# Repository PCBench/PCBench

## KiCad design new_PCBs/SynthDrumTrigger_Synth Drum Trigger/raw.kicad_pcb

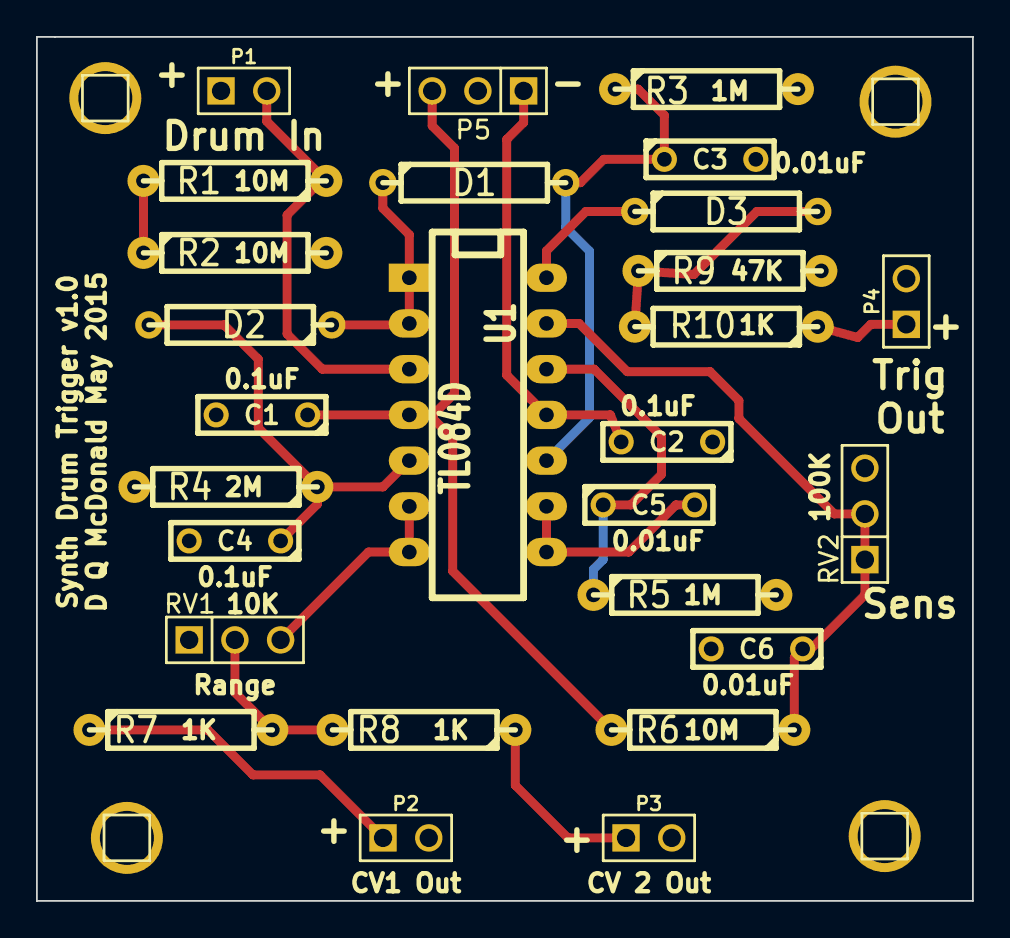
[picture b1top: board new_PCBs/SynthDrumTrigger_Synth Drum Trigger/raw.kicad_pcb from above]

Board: 2 copper layers, 52.0 x 48.0 mm, 27 parts (0 on the bottom side), 18 nets.

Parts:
C1, C2, C4: 0.1uF; C2
C3, C6: 0.01uF; C2
C5: 0.01; C2
D1, D2, D3: DIODE; R4
P1, P2, P3, P4: CONN_2; PIN_ARRAY_2X1
P5: Power_In; PIN_ARRAY_3X1
R1, R2, R6: 10M; R4-LARGE_PADS
R3, R5: 1M; R4-LARGE_PADS
R4: 2M; R4-LARGE_PADS
R7, R8, R10: 1K; R4-LARGE_PADS
R9: 47K; R4-LARGE_PADS
RV1: 10K; PIN_ARRAY_3X1
RV2: 100K; PIN_ARRAY_3X1
U1: TL084D; DIP-14__300_ELL

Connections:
+12V: C1.1, P5.3, R6.2, U1.4
-12V: C2.2, P5.1, U1.11
GND: C1.2, C2.1, C3.2, C4.2, C6.2, P1.1, P2.2, P3.2, P4.2, P5.2, R2.2, R3.2, R4.2, R5.2, R9.2, RV1.1, RV2.3
unnamed: C3.1, D1.2, R3.1, U1.10
unnamed: C4.1, D2.2, R4.1, U1.5
unnamed: C5.1, R5.1, U1.12
unnamed: C5.2, U1.8, U1.9
unnamed: C6.1, R6.1, RV2.1, RV2.2, U1.13
unnamed: D1.1, D2.1, U1.1, U1.2
unnamed: D3.1, U1.14
unnamed: D3.2, R9.1, R10.2
unnamed: P1.2, R1.1, U1.3
unnamed: P2.1, R7.1
unnamed: P3.1, R8.1
unnamed: P4.1, R10.1
unnamed: R1.2, R2.1
unnamed: R7.2, R8.2, RV1.2
unnamed: RV1.3, U1.6, U1.7

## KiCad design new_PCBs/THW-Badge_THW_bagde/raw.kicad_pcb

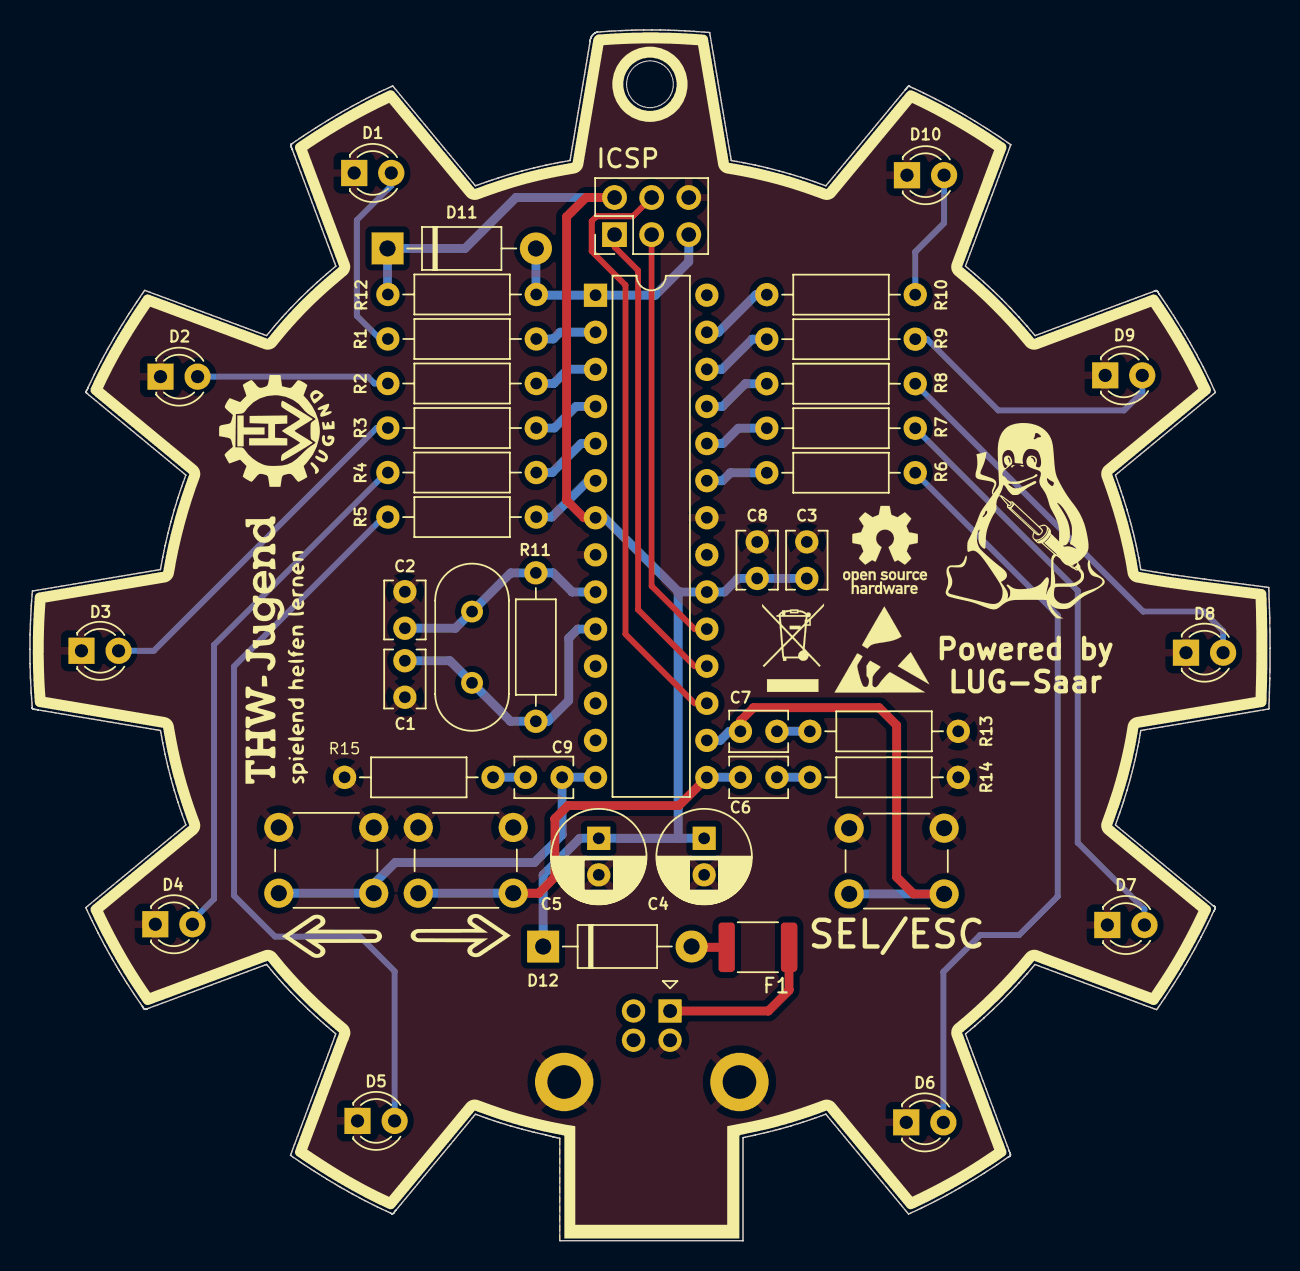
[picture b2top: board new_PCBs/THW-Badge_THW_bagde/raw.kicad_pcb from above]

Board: 2 copper layers, 84.9 x 82.9 mm, 44 parts (0 on the bottom side), 36 nets.

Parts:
C1, C2: C; C_Disc_D3.8mm_W2.6mm_P2.50mm
C3, C6, C7, C8, C9: 100n; C_Disc_D3.8mm_W2.6mm_P2.50mm
C4, C5: 100u; CP_Radial_D6.3mm_P2.50mm
D1, D2, D3, D4, D5, D6, D7, D8, D9, D10: LED; LED_D3.0mm_Clear
D11, D12: D; D_DO-41_SOD81_P10.16mm_Horizontal
F1: MF-MSMF050-2; Fuse_1812_4532Metric
J1: USB_B; USB_B_Lumberg_2411_02_Horizontal
J2: ICSP; PinHeader_2x03_P2.54mm_Vertical
R1, R2, R3, R4, R5, R6, R7, R8, R9, R10: R; R_Axial_DIN0207_L6.3mm_D2.5mm_P10.16mm_Horizontal
R11: 1M; R_Axial_DIN0207_L6.3mm_D2.5mm_P10.16mm_Horizontal
R12: 10K; R_Axial_DIN0207_L6.3mm_D2.5mm_P10.16mm_Horizontal
R13, R14, R15: 100; R_Axial_DIN0207_L6.3mm_D2.5mm_P10.16mm_Horizontal
SW1, SW2, SW3: SW_Push; SW_PUSH_6mm
U1: ATmega328-P; DIP-28_W7.62mm
Y1: Crystal; Crystal_HC49-4H_Vertical

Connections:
+5V: C3.1, C4.1, C5.1, C8.1, D11.1 (K), D12.1 (K), J2.2, R12.2, U1.7 (VCC), U1.20 (AVCC)
/MISO: J2.1, U1.18 (PB4)
/MOSI: J2.4, U1.17 (PB3)
/PB0: C9.1, SW1.2, U1.14 (PB0)
/PB1: C6.1, SW2.2, U1.15 (PB1)
/PB2: C7.1, SW3.2, U1.16 (PB2)
/PC0: R6.1, U1.23 (PC0)
/PC1: R7.1, U1.24 (PC1)
/PC2: R8.1, U1.25 (PC2)
/PC3: R9.1, U1.26 (PC3)
/PC4: R10.1, U1.27 (PC4)
/PD0: R1.1, U1.2 (PD0)
/PD1: R2.1, U1.3 (PD1)
/PD2: R3.1, U1.4 (PD2)
/PD3: R4.1, U1.5 (PD3)
/PD4: R5.1, U1.6 (PD4)
/RES: D11.2 (A), J2.5, R12.1, U1.1 (~RESET/PC6)
/SCK: J2.3, U1.19 (PB5)
GND: C1.2, C2.2, C3.2, C4.2, C5.2, C8.2, D1.1 (K), D2.1 (K), D3.1 (K), D4.1 (K), D5.1 (K), D6.1 (K), D7.1 (K), D8.1 (K), D9.1 (K), D10.1 (K), J1.4 (GND), J1.5 (Shield), J2.6, R13.1, R14.1, R15.1, SW1.1, SW2.1, SW3.1, U1.8 (GND), U1.22 (GND)
unnamed: C1.1, R11.1, U1.10 (XTAL2/PB7), Y1.1
unnamed: C2.1, R11.2, U1.9 (XTAL1/PB6), Y1.2
unnamed: C7.2, R13.2
unnamed: C9.2, R15.2
unnamed: D1.2 (A), R1.2
unnamed: D2.2 (A), R2.2
unnamed: D3.2 (A), R3.2
unnamed: D4.2 (A), R4.2
unnamed: D5.2 (A), R5.2
unnamed: D6.2 (A), R6.2
unnamed: D7.2 (A), R7.2
unnamed: D8.2 (A), R8.2
unnamed: D9.2 (A), R9.2
unnamed: D10.2 (A), R10.2
unnamed: D12.2 (A), F1.2
unnamed: F1.1, J1.1 (VBUS)
unnamed: C6.2, R14.2

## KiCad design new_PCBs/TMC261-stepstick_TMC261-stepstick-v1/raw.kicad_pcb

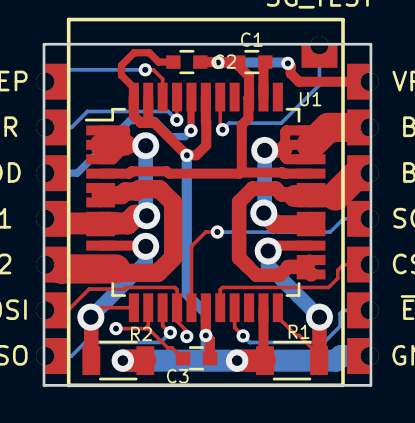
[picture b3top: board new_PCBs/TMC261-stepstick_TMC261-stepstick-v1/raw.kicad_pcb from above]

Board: 2 copper layers, 18.2 x 18.9 mm, 21 parts (0 on the bottom side), 19 nets.

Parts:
C1, C2: 100nF; C_0603
C3: 470nF; C_0603
P1: VDD; smd-edge
P2: MISO; smd-edge
P3: MOSI; smd-edge
P4: SCK; smd-edge
P5: ~EN; smd-edge
P6: CSN; smd-edge
P7: STEP; smd-edge
P8: DIR; smd-edge
P9: SG_TEST; smd-edge
P10: VPP; smd-edge
P11: GND; smd-edge
P12: B1; smd-edge
P13: B2; smd-edge
P14: A2; smd-edge
P15: A1; smd-edge
R1, R2: 150mR; C_1206
U1: TMC261; LQFP-44_10x10mm_Pitch0.8mm

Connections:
A1: P15.1, U1.1, U1.2, U1.3, U1.7, U1.8
A2: P14.1, U1.5, U1.6, U1.10, U1.11
B1: P12.1, U1.26, U1.27, U1.31, U1.32, U1.33
B2: P13.1, U1.23, U1.24, U1.28, U1.29
CSN: P6.1, U1.18
DIR: P8.1, U1.41
GND: C2.2, C3.2, P11.1, R1.2, R2.2, U1.17, U1.21, U1.39, U1.43, U1.44
MISO: P2.1, U1.14
MOSI: P3.1, U1.15
unnamed: C1.2, U1.35
unnamed: C3.1, U1.13
unnamed: R1.1, U1.22, U1.25
unnamed: R2.1, U1.9, U1.12
SCK: P4.1, U1.16
SG_TEST: P9.1, U1.38
STEP: P7.1, U1.42
VDD: P1.1, U1.40
VPP: C1.1, C2.1, P10.1, U1.4, U1.30, U1.36
~EN: P5.1, U1.19

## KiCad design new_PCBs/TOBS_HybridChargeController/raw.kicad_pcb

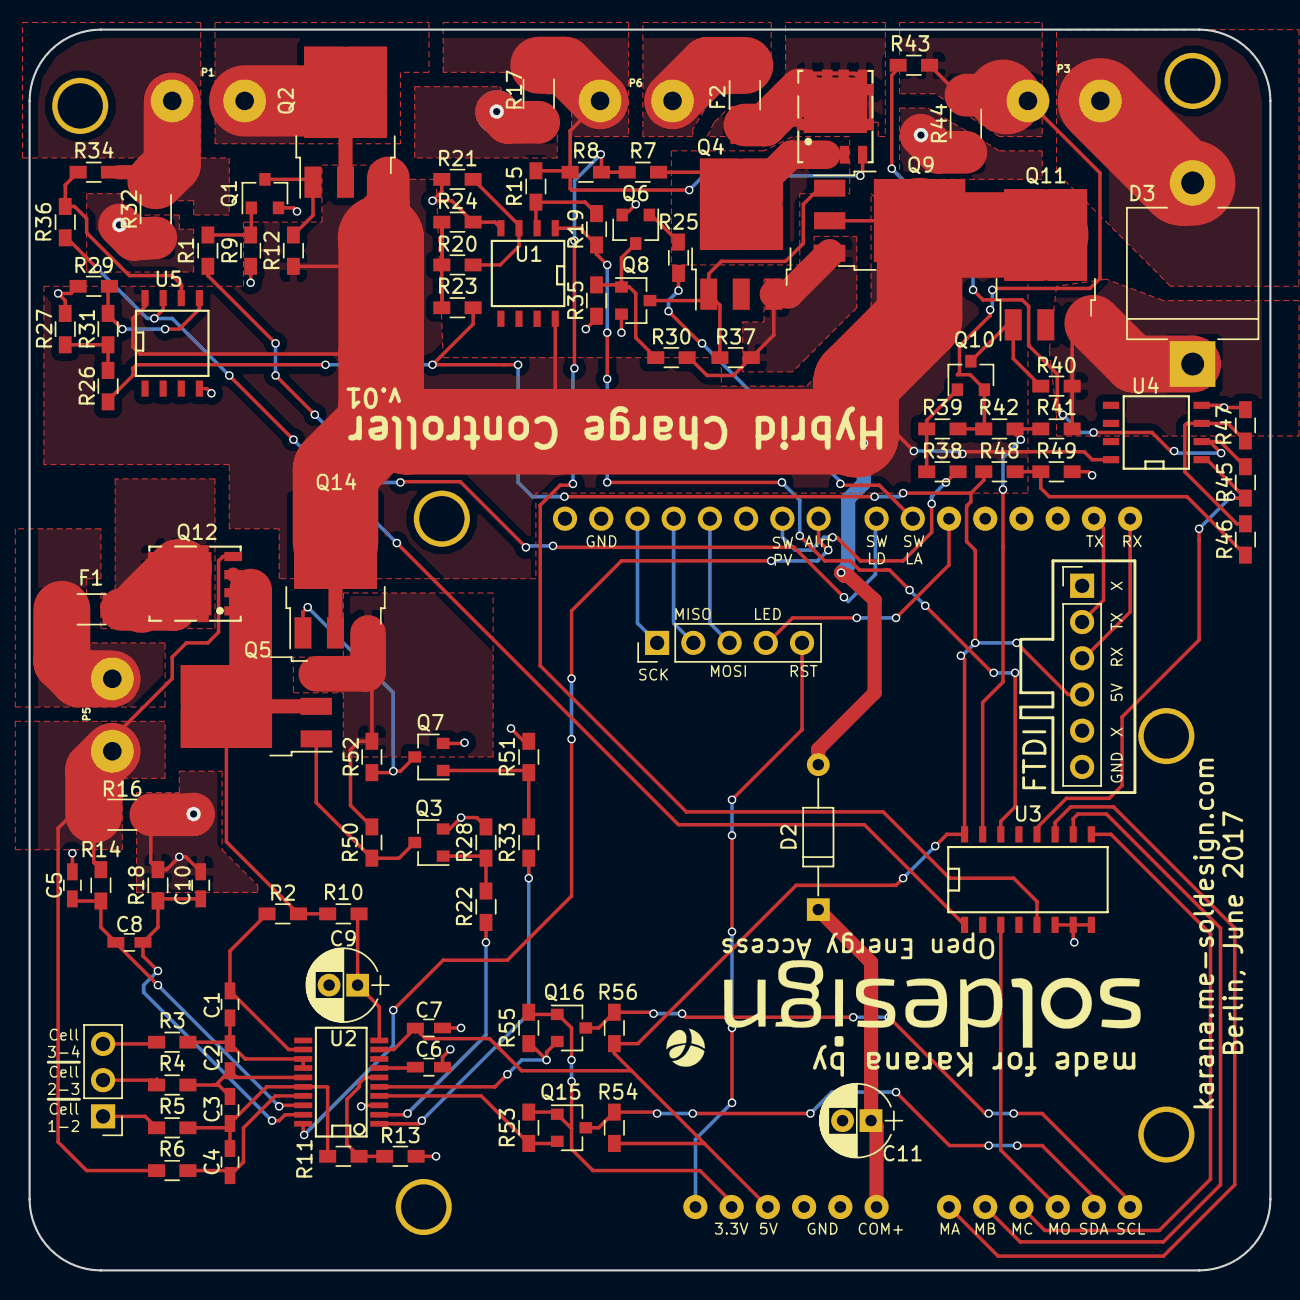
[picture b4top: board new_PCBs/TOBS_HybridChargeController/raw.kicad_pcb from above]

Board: 2 copper layers, 87.0 x 87.0 mm, 100 parts (0 on the bottom side), 79 nets.

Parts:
AU1: Uno Layout; ARDUINO_SHIELD_bigger_holes_no_outline
C1, C2, C3, C4, C6, C7: 1µ; C_0603_HandSoldering
C5, C8, C10: 0.1µ; C_0603_HandSoldering
C9, C11: 10µ; CP_Radial_D5.0mm_P2.00mm
D2: 1N4148-T; D_DO-35_SOD27_P10.16mm_Horizontal
D3: VSB2045Y-M3/54; D_P600_R-6_P12.70mm_Horizontal
F1, F2: 15A; Fuse_SMD1206_HandSoldering
P1: Load; TerminalBlock_Screw_2pol
P2: LI_balancer; Pin_Header_Straight_1x03_Pitch2.54mm
P3: PV; TerminalBlock_Screw_2pol
P4: Extra; Pin_Header_Straight_1x05_Pitch2.54mm
P5: LI; TerminalBlock_Screw_2pol
P6: LA; TerminalBlock_Screw_2pol
P7: FTDI; Pin_Header_Straight_1x06_Pitch2.54mm
Q1, Q3, Q6, Q7, Q8, Q10: MMBT3904; SOT-23
Q2, Q4, Q5, Q9, Q11, Q14: IPD90P04P4L-04; TO-252-3_TabPin2
Q12, Q13: STL60P4LLF6; powerFLAT_5x6_5..8com
Q15, Q16: BSS138; SOT-23
R1, R11, R13, R22, R23, R24, R25, R26, R27, R33, R38, R48, R49, R53, R54, R55, R56: 10k; R_0603_HandSoldering
R2, R3, R4, R5, R6, R10, R14, R18: 100; R_0603_HandSoldering
R7, R9, R28, R35, R39, R41, R51: 100k; R_0603_HandSoldering
R8, R42: 33k; R_0603_HandSoldering
R12, R30, R37, R50, R52: 47k; R_0603_HandSoldering
R15, R21, R29, R34, R43, R47: 4.7k; R_0603_HandSoldering
R16, R17, R32, R44: R005; R_1206_HandSoldering
R19, R20, R31, R36, R45, R46: 220k; R_0603_HandSoldering
R40: 2.2k; R_0603_HandSoldering
U1, U4, U5: LM358D; SOIC-8-N
U2: bq76920; SSOP-20
U3: cd4051; SO-16-N

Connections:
/3.3V: AU1.3V3, Q15.1, Q16.1, R53.1, R55.1
/5V: AU1.5V, C7.1, P7.4, R23.1, R26.1, R48.1, R54.1, R56.1, U2.9, U3.16
/Alert: AU1.8, U2.20
/CELL12: P2.1, R5.2
/CELL23: P2.2, R4.2
/CELL34: P2.3, R3.2
/CHG: R22.2, U2.2
/COM+: D2.2, Q2.3, Q9.2, Q11.2, Q14.2, R12.2, U1.8, U4.8, U5.8
/DSG: R33.2, U2.1
/GND: AU1.GND1, AU1.GND2, AU1.GND3, C5.2, C6.2, C7.2, C9.2, C10.2, C11.2, P7.6, Q1.2, Q3.2, Q6.2, Q7.2, Q8.2, R9.1, R13.2, R16.1, R17.1, R18.1, R21.1, R24.2, R27.2, R28.1, R29.1, R32.1, R35.1, R44.1, R47.1, R49.2, R51.1, U1.4, U2.3, U3.6, U3.7, U3.8, U4.4, U5.4
/LA+: Q4.2, Q13.1, Q13.2, Q13.3, R7.1
/LA-: P6.1, Q13.4, R8.2, R15.1, R17.2
/LED_BTN: AU1.5, P4.4
/LI+: Q5.2, Q12.1, Q12.2, Q12.3, R2.2, R10.2
/LI-: P5.1, Q12.4, R6.2, R14.1, R16.2
/LOAD+: P1.2, Q2.2
/LOAD-: P1.1, R32.2, R34.1
/MISO: AU1.12, P4.2
/MOSI: AU1.11, P4.3
/MplexA: AU1.A0, U3.11
/MplexB: AU1.A1, U3.10
/MplexC: AU1.A2, U3.9
/MplexOut: AU1.A3, U3.3
/PV+: D3.1, Q11.3, R40.2, R41.1
/PV-: P3.1, Q10.2, R39.1, R42.2, R43.1, R44.2
/RST: AU1.RST, P4.5
/RX: AU1.0, P7.3
/SCK: AU1.13, P4.1
/SCL3: Q16.2, R55.2, U2.5
/SCL5: AU1.A5, Q16.3, R56.2
/SDA3: Q15.2, R53.2, U2.4
/SDA5: AU1.A4, Q15.3, R54.2
/SRN: C8.1, C10.1, R18.2, U2.19
/SRP: C5.1, C8.2, R14.2, U2.18
/SW_LA: AU1.6, R25.2
/SW_LD: AU1.7, R1.2
/SW_PV: AU1.9, R38.2
/S_LA_I: R19.1, U1.1, U3.14
/S_LA_V: R7.2, R8.1, U3.5
/S_LD_I: R36.2, U3.1, U5.7
/S_PV_I: R45.1, U3.12, U4.1
/S_PV_V: R41.2, R42.1, U3.15
/TX: AU1.1, P7.2
/VC0: C4.2, R6.1, U2.17
/VC1: C3.2, C4.1, R5.1, R11.2, U2.16
/VC2: C2.2, C3.1, R4.1, U2.15
/VC3: C1.2, C2.1, R3.1, U2.13, U2.14
/VC5: C1.1, R2.1, U2.12
unnamed: AU1.V_IN, C11.1, D2.1
unnamed: C6.1, U2.7
unnamed: C9.1, R10.1, U2.10
unnamed: D3.2, P3.2
unnamed: F1.1, P5.2
unnamed: F1.2, Q12.5, Q12.6, Q12.7, Q12.8
unnamed: F2.1, P6.2
unnamed: F2.2, Q13.5, Q13.6, Q13.7, Q13.8
unnamed: Q1.1, R1.1, R9.2
unnamed: Q1.3, Q2.1, R12.1
unnamed: Q3.1, R22.1, R28.2
unnamed: Q3.3, Q5.1, R50.2
unnamed: Q4.1, Q8.3, Q9.1, R37.1
unnamed: Q4.3, Q9.3, R30.2, R37.2
unnamed: Q6.1, R25.1
unnamed: Q6.3, Q8.1, R30.1, R35.2
unnamed: Q7.1, R33.1, R51.2
unnamed: Q10.1, R38.1, R39.2
unnamed: Q10.3, Q11.1, R40.1
unnamed: Q7.3, Q14.1, R52.1
unnamed: Q5.3, Q14.3, R50.1, R52.2
unnamed: R11.1, R13.1, U2.6
unnamed: R15.2, R19.2, U1.2
unnamed: R20.1, R23.2, R24.1
unnamed: R20.2, R21.2, U1.3
unnamed: R26.2, R27.1, R31.1
unnamed: R29.2, R31.2, U5.5
unnamed: R34.2, R36.1, U5.6
unnamed: R43.2, R45.2, U4.2
unnamed: R46.1, R48.2, R49.1
unnamed: R46.2, R47.2, U4.3

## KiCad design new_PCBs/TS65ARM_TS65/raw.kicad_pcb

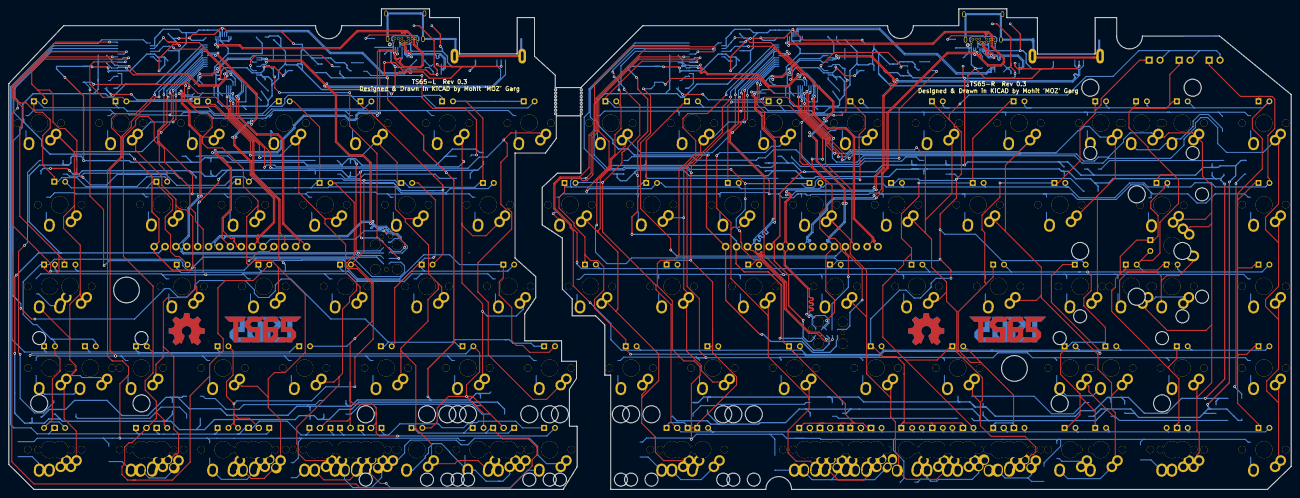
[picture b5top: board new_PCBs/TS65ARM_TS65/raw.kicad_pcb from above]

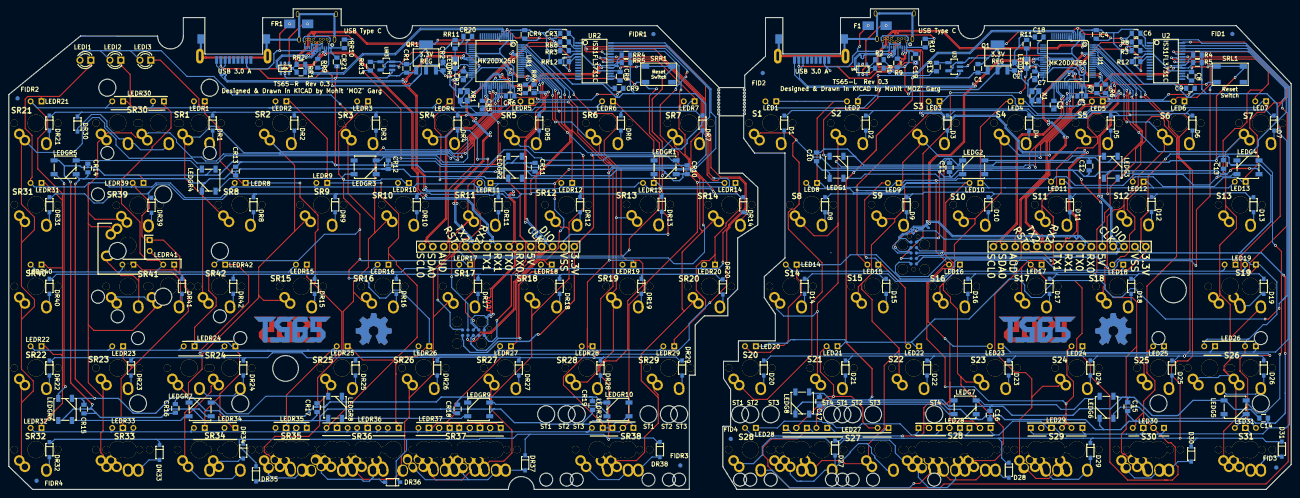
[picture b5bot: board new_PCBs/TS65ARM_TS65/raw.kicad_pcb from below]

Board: 2 copper layers, 299.2 x 112.1 mm, 438 parts (198 on the bottom side), 208 nets.

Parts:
BREAKHOLES1, BREAKHOLES2: MISC; BreakHoles
C1, C2, C3: 1uF; SMD_0805
C4, C5, C6, C7, C8, C18: 0.1uF; SMD_0805
C9: 0.22uF; SMD_0805
C10, C11, C12, C13, C14, C15, C16, C17: 0.1 uF; SMD_0805
C19: 10uF; SMD_0805
CR1, CR2, CR3: 1uF; SMD_0805
CR4, CR5, CR6, CR7, CR8, CR20: 0.1uF; SMD_0805
CR9: 0.22uF; SMD_0805
CR10, CR11, CR12, CR13, CR14, CR15, CR16, CR17, CR18, CR19: 0.1 uF; SMD_0805
CR21: 10uF; SMD_0805
D1, D2, D3, D4, D5, D6, D7, D8, D9, D10, D11, D12, D13, D14, D15, D16, D17, D18, D19, D20, D21, D22, D23, D24, D25, D26, D27, D28, D29, D30, D31: DIODE; SOD123-DIODE
DR1, DR2, DR3, DR4, DR5, DR6, DR7, DR8, DR9, DR10, DR11, DR12, DR13, DR14, DR15, DR16, DR17, DR18, DR19, DR20, DR21, DR22, DR23, DR24, DR25, DR26, DR27, DR28, DR29, DR30, DR31, DR32, DR33, DR34, DR35, DR36, DR37, DR38, DR39, DR40, DR41, DR42: DIODE; SOD123-DIODE
F1: PTC FUSE; Fuse_SMD1206_HandSoldering
FID1, FID2, FID3, FID4: MISC; FID
FIDR1, FIDR2, FIDR3, FIDR4: MISC; FID
FR1: PTC FUSE; Fuse_SMD1206_HandSoldering
HOLE1: MISC; FID
HOLER1: MISC; FID
LED1, LED2, LED3, LED4, LED5, LED6, LED7, LED8, LED9, LED10, LED11, LED12, LED13, LED14, LED15, LED16, LED17, LED18, LED19, LED19_2, LED20, LED21, LED22, LED23, LED24, LED25, LED26, LED26_2, LED27, LED27_2, LED27_3, LED27_4, LED28, LED28_2, LED28_3, LED28_4, LED28_5, LED28_6, LED28_7, LED29, LED29_2, LED29_3, LED29_4, LED30, LED30_2, LED30_3, LED31, LED31_2: LED; INSW_LEDS_REG
LEDD1: LED; LED_0805
LEDDR1: LED; LED_0805
LEDG1, LEDG2, LEDG3, LEDG4, LEDG5, LEDG6, LEDG7, LEDG8: WS2812B
LEDGR1, LEDGR2, LEDGR3, LEDGR4, LEDGR5, LEDGR6, LEDGR7, LEDGR8, LEDGR9, LEDGR10: WS2812B
LEDI1, LEDI2, LEDI3: LED; LED-3MM
LEDR1, LEDR2, LEDR3, LEDR4, LEDR5, LEDR6, LEDR7, LEDR8, LEDR9, LEDR10, LEDR11, LEDR12, LEDR13, LEDR14, LEDR15, LEDR16, LEDR17, LEDR18, LEDR19, LEDR20, LEDR21, LEDR22, LEDR23, LEDR24, LEDR24_2, LEDR25, LEDR26, LEDR27, LEDR28, LEDR29, LEDR30, LEDR30_2, LEDR31, LEDR32, LEDR33, LEDR33_2, LEDR34, LEDR34_2, LEDR35, LEDR35_2, LEDR35_3, LEDR36, LEDR36_2, LEDR36_3, LEDR36_4, LEDR36_5, LEDR37, LEDR37_2, LEDR37_3, LEDR37_4, LEDR37_5, LEDR37_6, LEDR37_7, LEDR38, LEDR38_2, LEDR38_3, LEDR39, LEDR40, LEDR41, LEDR41_2, LEDR41_3, LEDR42: LED; INSW_LEDS_REG
LOGO1, LOGO2: MISC; TS65-LOGO
LOGO3, LOGO4: MISC; OSHW
LOGOR1, LOGOR2: MISC; TS65-LOGO
LOGOR3, LOGOR4: MISC; OSHW
P1: USB_TYPE_C; USB_TYPE_C_HYBRID
P2: USB3_AFEMALE; USB3_AFEMALE_MOD
P3: CONN_15; HEADER_1x15
P4: FLASH_HDR; JLINK_NEEDLE
PR1: USB_TYPE_C; USB_TYPE_C_HYBRID
PR2: USB3_AFEMALE; USB3_AFEMALE_MOD
PR3: CONN_15; HEADER_1x15
PR4: FLASH_HDR; JLINK_NEEDLE
Q1: 3.3V REG IC; SOT-223
QR1: 3.3V REG IC; SOT-223
R1, R2: 33; SMD_0805
R3, R4, R5: 4.7k; SMD_0805
R6, R7: 100; SMD_0805
R8: 100k; SMD_0805
R9, R10: 5.1k; SMD_0805
R11: 1k; SMD_0805
R12: 20k; SMD_0805
R13: 330; SMD_0805
RR1, RR2: 33; SMD_0805
RR3, RR4, RR5: 4.7k; SMD_0805
RR6, RR7: 100; SMD_0805
RR8: 100k; SMD_0805
RR9, RR10: 5.1k; SMD_0805
RR11: 1k; SMD_0805
RR12: 20k; SMD_0805
RR13: 330; SMD_0805
S1, S2, S3, S4, S5, S6, S7, S8, S9, S10, S11, S12, S13, S14, S15, S16, S17, S18, S19, S19_2, S20, S21, S22, S23, S24, S25, S26, S26_2, S27, S27_2, S27_3, S27_4, S28, S28_2, S28_3, S28_4, S28_5, S28_6, S28_7, S29, S29_2, S29_3, S29_4, S30, S30_2, S30_3, S31, S31_2: SW; MXALPS2
SR1, SR2, SR3, SR4, SR5, SR6, SR7, SR8, SR9, SR10, SR11, SR12, SR13, SR14, SR15, SR16, SR17, SR18, SR19, SR20, SR21, SR22, SR23, SR24, SR24_2, SR25, SR26, SR27, SR28, SR29, SR30, SR30_2, SR31, SR32, SR33, SR33_2, SR34, SR34_2, SR35, SR35_2, SR35_3, SR36, SR36_2, SR36_3, SR36_4, SR36_5, SR37, SR37_2, SR37_3, SR37_4, SR37_5, SR37_6, SR37_7, SR38, SR38_2, SR38_3, SR39, SR40, SR41, SR41_2, SR41_3, SR42: SW; MXALPS2
SRL1: TAC_SWITCH; TACT_5.2x5.2
SRR1: TAC_SWITCH; TACT_5.2x5.2
STAB1, STAB2, STAB3, STAB4, STAB5: MISC; MX_200
STABR1, STABR2, STABR3, STABR4, STABR5, STABR6, STABR7: MISC; MX_200
U1: MK20DX256VLH7; LQFP64
U2: IS31FL3731; SSOP-28
U3: 74HCT1G125; SOT-753
U4: IP4234CZ6; SOT457
UR1: MK20DX256VLH7; LQFP64
UR2: IS31FL3731; SSOP-28
UR3: 74HCT1G125; SOT-753
UR4: IP4234CZ6; SOT457
X1: CRYSTAL; NX3225SA
XR1: CRYSTAL; NX3225SA

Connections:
+5V: C1.1, C10.2, C11.2, C12.2, C13.2, C14.1, C15.1, C16.1, C17.1, C19.1, CR1.1, CR10.2, CR11.2, CR12.2, CR13.2, CR14.2, CR15.1, CR16.1, CR17.1, CR18.1, CR19.1, CR21.1, F1.2, FR1.2, LEDG1.1, LEDG2.1, LEDG3.1, LEDG4.1, LEDG5.1, LEDG6.1, LEDG7.1, LEDG8.1, LEDGR1.1, LEDGR2.1, LEDGR3.1, LEDGR4.1, LEDGR5.1, LEDGR6.1, LEDGR7.1, LEDGR8.1, LEDGR9.1, LEDGR10.1, P3.5, P4.5, PR3.5, PR4.5, Q1.1, QR1.1, U3.1, U4.5, UR3.1, UR4.5
/ledmatrix/CA1: LED1.2, LED2.1, LED3.1, LED4.1, LED5.1, LED6.2, LED10.2, LED15.2, LED23.2, LED28.2, LED28_2.2, LED28_3.2, LED28_4.2, LED28_5.2, LED28_6.2, LED28_7.2, U2.21
/ledmatrix/CA2: LED1.1, LED2.2, LED7.2, LED8.1, LED9.1, LED11.2, LED16.2, LED24.2, LED29.2, LED29_2.2, LED29_3.2, LED29_4.2, U2.22
/ledmatrix/CA3: LED3.2, LED6.1, LED7.1, LED12.2, LED13.1, LED14.1, LED17.2, LED20.2, LED25.2, LED30.2, LED30_2.2, LED30_3.2, U2.23
/ledmatrix/CA4: LED4.2, LED8.2, LED10.1, LED11.1, LED12.1, LED13.2, LED18.2, LED19.1, LED19_2.1, LED21.2, LED26.2, LED26_2.2, LED27.2, LED27_2.2, LED27_3.2, LED27_4.2, LED31.2, LED31_2.2, U2.24
/ledmatrix/CA5: LED5.2, LED9.2, LED14.2, LED15.1, LED16.1, LED17.1, LED18.1, LED19.2, LED19_2.2, LED22.2, U2.25
/ledmatrix/CA6: LED20.1, LED21.1, LED22.1, U2.26
/ledmatrix/CA7: LED23.1, LED24.1, LED25.1, LED26.1, LED26_2.1, U2.27
/ledmatrix/CA8: LED27.1, LED27_2.1, LED27_3.1, LED27_4.1, U2.28
/ledmatrix/CA9: LED28.1, LED28_2.1, LED28_3.1, LED28_4.1, LED28_5.1, LED28_6.1, LED28_7.1, LED29.1, LED29_2.1, LED29_3.1, LED29_4.1, LED30.1, LED30_2.1, LED30_3.1, LED31.1, LED31_2.1, U2.1
/ledmatrixR/CA1: LEDR1.2, LEDR2.2, LEDR3.2, LEDR4.2, LEDR5.2, LEDR6.2, LEDR7.1, LEDR21.2, LEDR22.1, LEDR30.2, LEDR30_2.2, LEDR31.1, LEDR32.1, LEDR40.1, UR2.21
/ledmatrixR/CA2: LEDI1.1, LEDR8.2, LEDR9.2, LEDR10.2, LEDR11.2, LEDR12.2, LEDR13.2, LEDR21.1, LEDR23.1, LEDR31.2, LEDR33.1, LEDR33_2.1, LEDR39.2, LEDR41.1, LEDR41_2.1, LEDR41_3.1, UR2.22
/ledmatrixR/CA3: LEDI2.1, LEDR15.2, LEDR16.2, LEDR17.2, LEDR18.2, LEDR19.2, LEDR20.2, LEDR24.1, LEDR24_2.1, LEDR30.1, LEDR30_2.1, LEDR34.1, LEDR34_2.1, LEDR39.1, LEDR40.2, LEDR41.2, LEDR41_2.2, LEDR41_3.2, UR2.23
/ledmatrixR/CA4: LEDI3.1, LEDR1.1, LEDR8.1, LEDR15.1, LEDR22.2, LEDR23.2, LEDR24.2, LEDR24_2.2, LEDR25.2, LEDR26.2, LEDR27.2, LEDR28.2, LEDR29.2, LEDR35.1, LEDR35_2.1, LEDR35_3.1, UR2.24
/ledmatrixR/CA5: LEDR2.1, LEDR9.1, LEDR14.2, LEDR16.1, LEDR25.1, LEDR32.2, LEDR33.2, LEDR33_2.2, LEDR34.2, LEDR34_2.2, LEDR35.2, LEDR35_2.2, LEDR35_3.2, LEDR36.2, LEDR36_2.2, LEDR36_3.2, LEDR36_4.2, LEDR36_5.2, LEDR37.2, LEDR37_2.2, LEDR37_3.2, LEDR37_4.2, LEDR37_5.2, LEDR37_6.2, LEDR37_7.2, LEDR38.2, LEDR38_2.2, LEDR38_3.2, UR2.25
/ledmatrixR/CA6: LEDI1.2, LEDI2.2, LEDI3.2, LEDR3.1, LEDR7.2, LEDR10.1, LEDR17.1, LEDR26.1, LEDR36.1, LEDR36_2.1, LEDR36_3.1, LEDR36_4.1, LEDR36_5.1, LEDR42.2, UR2.26
/ledmatrixR/CA7: LEDR4.1, LEDR11.1, LEDR18.1, LEDR27.1, LEDR37.1, LEDR37_2.1, LEDR37_3.1, LEDR37_4.1, LEDR37_5.1, LEDR37_6.1, LEDR37_7.1, UR2.27
/ledmatrixR/CA8: LEDR5.1, LEDR12.1, LEDR19.1, LEDR28.1, LEDR38.1, LEDR38_2.1, LEDR38_3.1, UR2.28
/ledmatrixR/CA9: LEDR6.1, LEDR13.1, LEDR14.1, LEDR20.1, LEDR29.1, LEDR42.1, UR2.1
/mcu/AUD: C9.2, P3.13
/mcu/GND: P1.0, P2.10
/mcu/INTB: R3.2, U1.40, U2.4
/mcu/MCU_RESET: C5.1, P3.12, P4.10, SRL1.2, U1.34
/mcu/PTA5: LEDD1.1, P4.9, U1.27
/mcu/PTA13: U1.29, U3.2
/mcu/PTB18: S1.1, S20.1, U1.41
/mcu/PTB19: S2.1, S8.1, S14.1, S21.1, U1.42
/mcu/PTC0: S3.1, S9.1, S15.1, S22.1, S27.1, S27_2.1, S27_3.1, S27_4.1, U1.43
/mcu/PTC9: S4.1, S10.1, S16.1, S23.1, S28.1, S28_2.1, S28_3.1, S28_4.1, S28_5.1, S28_6.1, S28_7.1, U1.54
/mcu/PTC10: S5.1, S11.1, S17.1, S24.1, S29.1, S29_2.1, S29_3.1, S29_4.1, U1.55
/mcu/PTC11: S6.1, S12.1, S18.1, S25.1, S30.1, S30_2.1, S30_3.1, U1.56
/mcu/PTD0: S7.1, S13.1, S19.1, S19_2.1, S26.1, S26_2.1, S31.1, S31_2.1, U1.57
/mcu/PTD1: D1.2, D2.2, D3.2, D4.2, D5.2, D6.2, D7.2, U1.58
/mcu/PTD4: D8.2, D9.2, D10.2, D11.2, D12.2, D13.2, U1.61
/mcu/PTD5: D14.2, D15.2, D16.2, D17.2, D18.2, D19.2, U1.62
/mcu/PTD6: D20.2, D21.2, D22.2, D23.2, D24.2, D25.2, D26.2, U1.63
/mcu/PTD7: D27.2, D28.2, D29.2, D30.2, D31.2, U1.64
/mcu/SCL0: P3.15, R4.2, U1.35, U2.20
/mcu/SDA0: P3.14, R5.2, U1.36, U2.19
/mcu/SDB: R8.2, U1.39, U2.3
/mcu/SWD_CLK: P3.4, P4.4, R6.2
/mcu/SWD_DIO: P3.3, P4.2, R7.2
/mcu/UART0+: P2.5, P3.7, P4.6, U1.24
/mcu/UART0-: P2.6, P3.6, P4.8, U1.23
/mcu/UART1+: P1.A2, P1.B2, P3.9, U1.1
/mcu/UART1-: P1.A3, P1.B3, P3.8, U1.2
/mcu/UART2+: P3.11, P4.7, U1.60
/mcu/UART2-: P3.10, U1.59
/mcu/USB_D+: R2.2, U1.5
/mcu/USB_D-: R1.2, U1.6
/mcu/USB_D_IN+: P1.A6, P1.B6, U4.3
/mcu/USB_D_IN-: P1.A7, P1.B7, U4.4
/mcu/VBUS: F1.1, P1.A4, P1.A9, P1.B4, P1.B9, P2.1
/mcuR/AUD: CR9.2, PR3.13
/mcuR/GND: PR1.0, PR2.10
/mcuR/INTB: RR3.2, UR1.40, UR2.4
/mcuR/MCU_RESET: CR5.1, PR3.12, PR4.10, SRR1.2, UR1.34
/mcuR/PTA5: LEDDR1.1, PR4.9, UR1.27
/mcuR/PTA13: UR1.29, UR3.2
/mcuR/PTB2: SR21.1, SR22.1, SR31.1, SR32.1, SR40.1, UR1.37
/mcuR/PTB3: SR23.1, SR30.1, SR30_2.1, SR33.1, SR33_2.1, SR39.1, SR41.1, SR41_2.1, SR41_3.1, UR1.38
/mcuR/PTB18: SR1.1, SR8.1, SR42.1, UR1.41
/mcuR/PTB19: SR2.1, SR9.1, SR15.1, SR24.1, SR24_2.1, SR34.1, SR34_2.1, UR1.42
/mcuR/PTC0: SR3.1, SR10.1, SR16.1, SR25.1, SR35.1, SR35_2.1, SR35_3.1, UR1.43
/mcuR/PTC9: SR4.1, SR11.1, SR17.1, SR26.1, SR36.1, SR36_2.1, SR36_3.1, SR36_4.1, SR36_5.1, UR1.54
/mcuR/PTC10: SR5.1, SR12.1, SR18.1, SR27.1, SR37.1, SR37_2.1, SR37_3.1, SR37_4.1, SR37_5.1, SR37_6.1, SR37_7.1, UR1.55
/mcuR/PTC11: SR6.1, SR13.1, SR19.1, SR28.1, UR1.56
/mcuR/PTD0: SR7.1, SR14.1, SR20.1, SR29.1, SR38.1, SR38_2.1, SR38_3.1, UR1.57
/mcuR/PTD1: DR1.2, DR2.2, DR3.2, DR4.2, DR5.2, DR6.2, DR7.2, DR21.2, DR30.2, UR1.58
/mcuR/PTD4: DR8.2, DR9.2, DR10.2, DR11.2, DR12.2, DR13.2, DR14.2, DR31.2, DR39.2, UR1.61
/mcuR/PTD5: DR15.2, DR16.2, DR17.2, DR18.2, DR19.2, DR20.2, DR40.2, DR41.2, DR42.2, UR1.62
/mcuR/PTD6: DR22.2, DR23.2, DR24.2, DR25.2, DR26.2, DR27.2, DR28.2, DR29.2, UR1.63
/mcuR/PTD7: DR32.2, DR33.2, DR34.2, DR35.2, DR36.2, DR37.2, DR38.2, UR1.64
/mcuR/SCL0: PR3.15, RR4.2, UR1.35, UR2.20
/mcuR/SDA0: PR3.14, RR5.2, UR1.36, UR2.19
/mcuR/SDB: RR8.2, UR1.39, UR2.3
/mcuR/SWD_CLK: PR3.4, PR4.4, RR6.2
/mcuR/SWD_DIO: PR3.3, PR4.2, RR7.2
/mcuR/UART0+: PR2.5, PR3.7, PR4.6, UR1.24
/mcuR/UART0-: PR2.6, PR3.6, PR4.8, UR1.23
/mcuR/UART1+: PR1.A2, PR1.B2, PR3.9, UR1.1
/mcuR/UART1-: PR1.A3, PR1.B3, PR3.8, UR1.2
/mcuR/UART2+: PR3.11, PR4.7, UR1.60
/mcuR/UART2-: PR3.10, UR1.59
/mcuR/USB_D+: RR2.2, UR1.5
/mcuR/USB_D-: RR1.2, UR1.6
/mcuR/USB_D_IN+: PR1.A6, PR1.B6, UR4.3
/mcuR/USB_D_IN-: PR1.A7, PR1.B7, UR4.4
/mcuR/VBUS: FR1.1, PR1.A4, PR1.A9, PR1.B4, PR1.B9, PR2.1
unnamed: C8.1, U2.16
unnamed: C9.1, U2.17
unnamed: CR8.1, UR2.16
unnamed: CR9.1, UR2.17
unnamed: D1.1, S1.2
unnamed: D2.1, S2.2
unnamed: D3.1, S3.2
unnamed: D4.1, S4.2
unnamed: D5.1, S5.2
unnamed: D6.1, S6.2
unnamed: D7.1, S7.2
unnamed: D8.1, S8.2
unnamed: D9.1, S9.2
unnamed: D10.1, S10.2
unnamed: D11.1, S11.2
unnamed: D12.1, S12.2
unnamed: D13.1, S13.2
unnamed: D14.1, S14.2
unnamed: D15.1, S15.2
unnamed: D16.1, S16.2
unnamed: D17.1, S17.2
unnamed: D18.1, S18.2
unnamed: D19.1, S19.2, S19_2.2
unnamed: D20.1, S20.2
unnamed: D21.1, S21.2
unnamed: D22.1, S22.2
unnamed: D23.1, S23.2
unnamed: D24.1, S24.2
unnamed: D25.1, S25.2
unnamed: D26.1, S26.2, S26_2.2
unnamed: D27.1, S27.2, S27_2.2, S27_3.2, S27_4.2
unnamed: D28.1, S28.2, S28_2.2, S28_3.2, S28_4.2, S28_5.2, S28_6.2, S28_7.2
unnamed: D29.1, S29.2, S29_2.2, S29_3.2, S29_4.2
unnamed: D30.1, S30.2, S30_2.2, S30_3.2
unnamed: D31.1, S31.2, S31_2.2
unnamed: DR1.1, SR1.2
unnamed: DR2.1, SR2.2
unnamed: DR3.1, SR3.2
unnamed: DR4.1, SR4.2
unnamed: DR5.1, SR5.2
unnamed: DR6.1, SR6.2
unnamed: DR7.1, SR7.2
unnamed: DR8.1, SR8.2
unnamed: DR9.1, SR9.2
unnamed: DR10.1, SR10.2
unnamed: DR11.1, SR11.2
unnamed: DR12.1, SR12.2
unnamed: DR13.1, SR13.2
unnamed: DR14.1, SR14.2
unnamed: DR15.1, SR15.2
unnamed: DR16.1, SR16.2
unnamed: DR17.1, SR17.2
unnamed: DR18.1, SR18.2
unnamed: DR19.1, SR19.2
unnamed: DR20.1, SR20.2
unnamed: DR21.1, SR21.2
unnamed: DR22.1, SR22.2
unnamed: DR23.1, SR23.2
unnamed: DR24.1, SR24.2, SR24_2.2
unnamed: DR25.1, SR25.2
unnamed: DR26.1, SR26.2
unnamed: DR27.1, SR27.2
unnamed: DR28.1, SR28.2
unnamed: DR29.1, SR29.2
unnamed: DR30.1, SR30.2, SR30_2.2
unnamed: DR31.1, SR31.2
unnamed: DR32.1, SR32.2
unnamed: DR33.1, SR33.2, SR33_2.2
unnamed: DR34.1, SR34.2, SR34_2.2
unnamed: DR35.1, SR35.2, SR35_2.2, SR35_3.2
unnamed: DR36.1, SR36.2, SR36_2.2, SR36_3.2, SR36_4.2, SR36_5.2
unnamed: DR37.1, SR37.2, SR37_2.2, SR37_3.2, SR37_4.2, SR37_5.2, SR37_6.2, SR37_7.2
unnamed: DR38.1, SR38.2, SR38_2.2, SR38_3.2
unnamed: DR39.1, SR39.2
unnamed: DR40.1, SR40.2
unnamed: DR41.1, SR41.2, SR41_2.2, SR41_3.2
unnamed: DR42.1, SR42.2
unnamed: LEDD1.2, R11.1
unnamed: LEDDR1.2, RR11.1
unnamed: LEDG1.2, LEDG2.4
unnamed: LEDG1.4, R13.1
unnamed: LEDG2.2, LEDG3.4
unnamed: LEDG3.2, LEDG4.4
unnamed: LEDG4.2, LEDG5.4
unnamed: LEDG5.2, LEDG6.4
unnamed: LEDG6.2, LEDG7.4
unnamed: LEDG7.2, LEDG8.4
unnamed: LEDGR1.2, LEDGR2.4
unnamed: LEDGR1.4, RR13.1
unnamed: LEDGR2.2, LEDGR3.4
unnamed: LEDGR3.2, LEDGR4.4
unnamed: LEDGR4.2, LEDGR5.4
unnamed: LEDGR5.2, LEDGR6.4
unnamed: LEDGR6.2, LEDGR7.4
unnamed: LEDGR7.2, LEDGR8.4
unnamed: LEDGR8.2, LEDGR9.4
unnamed: LEDGR9.2, LEDGR10.4
unnamed: P1.A5, R9.2
unnamed: P1.B5, R10.1
unnamed: PR1.A5, RR9.2
unnamed: PR1.B5, RR10.1
unnamed: R1.1, U4.6
unnamed: R2.1, U4.1
unnamed: R6.1, U1.22
unnamed: R7.1, U1.25
unnamed: R12.1, U2.6
unnamed: R13.2, U3.4
unnamed: RR1.1, UR4.6
unnamed: RR2.1, UR4.1
unnamed: RR6.1, UR1.22
unnamed: RR7.1, UR1.25
unnamed: RR12.1, UR2.6
unnamed: RR13.2, UR3.4
unnamed: U1.32, X1.1
unnamed: U1.33, X1.3
unnamed: UR1.32, XR1.1
unnamed: UR1.33, XR1.3
VDD: C2.1, C3.2, C4.1, C6.1, C7.1, C18.1, CR2.1, CR3.2, CR4.1, CR6.1, CR7.1, CR20.1, P3.1, P4.1, PR3.1, PR4.1, Q1.3, QR1.3, R3.1, R4.1, R5.1, RR3.1, RR4.1, RR5.1, U1.3, U1.7, U1.8, U1.21, U1.30, U1.48, U2.2, UR1.3, UR1.7, UR1.8, UR1.21, UR1.30, UR1.48, UR2.2
VSS: C1.2, C2.2, C3.1, C4.2, C5.2, C6.2, C7.2, C8.2, C10.1, C11.1, C12.1, C13.1, C14.2, C15.2, C16.2, C17.2, C18.2, C19.2, CR1.2, CR2.2, CR3.1, CR4.2, CR5.2, CR6.2, CR7.2, CR8.2, CR10.1, CR11.1, CR12.1, CR13.1, CR14.1, CR15.2, CR16.2, CR17.2, CR18.2, CR19.2, CR20.2, CR21.2, LEDG1.3, LEDG2.3, LEDG3.3, LEDG4.3, LEDG5.3, LEDG6.3, LEDG7.3, LEDG8.3, LEDGR1.3, LEDGR2.3, LEDGR3.3, LEDGR4.3, LEDGR5.3, LEDGR6.3, LEDGR7.3, LEDGR8.3, LEDGR9.3, LEDGR10.3, P1.A1, P1.A12, P1.B1, P1.B12, P2.4, P3.2, P4.3, PR1.A1, PR1.A12, PR1.B1, PR1.B12, PR2.4, PR3.2, PR4.3, Q1.2, QR1.2, R8.1, R9.1, R10.2, R11.2, R12.2, RR8.1, RR9.1, RR10.2, RR11.2, RR12.2, SRL1.3, SRL1.4, SRR1.3, SRR1.4, U1.4, U1.31, U1.47, U2.5, U2.18, U3.3, U3.5, U4.2, UR1.4, UR1.31, UR1.47, UR2.5, UR2.18, UR3.3, UR3.5, UR4.2, X1.2, X1.4, XR1.2, XR1.4

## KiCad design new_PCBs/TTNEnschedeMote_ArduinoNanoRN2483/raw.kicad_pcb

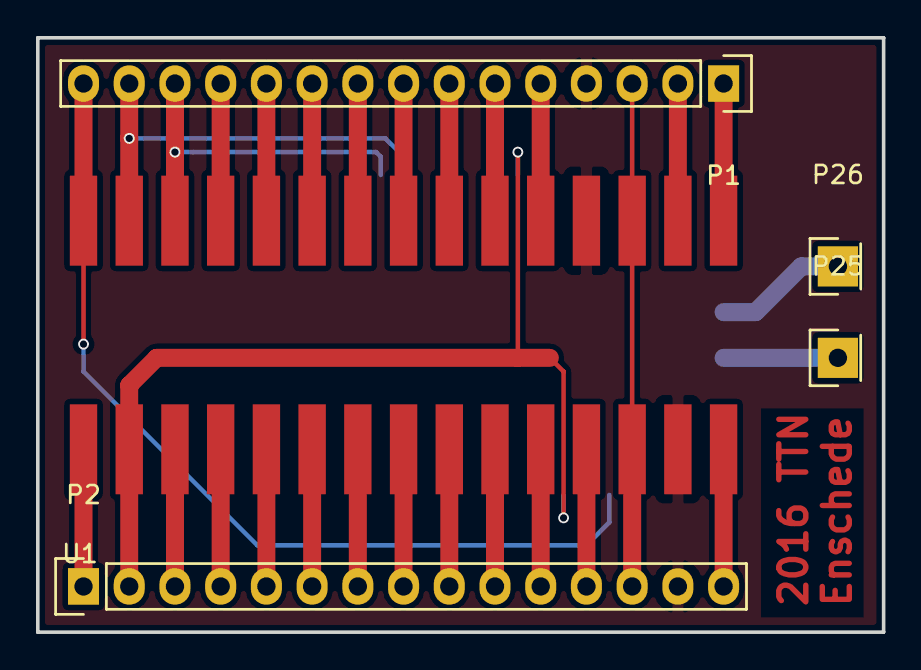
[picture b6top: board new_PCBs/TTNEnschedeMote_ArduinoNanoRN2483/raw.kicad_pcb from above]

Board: 2 copper layers, 47.0 x 33.0 mm, 6 parts (1 on the bottom side), 30 nets.

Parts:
P1, P2: CONN_01X15; Socket_Strip_Straight_1x15
P25, P26: CONN_01X01; Socket_Strip_Straight_1x01
U1: arduino_mini; SMT_ARDUINO_NANO
U2: RN2483

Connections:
/ARDUINO_3V: P2.2, U1.2, U2.12, U2.34
/P1: P2.1, U1.1
/P3: P2.3, U1.3
/P4: P2.4, U1.4
/P5: P2.5, U1.5
/P6: P2.6, U1.6
/P7: P2.7, U1.7
/P8: P2.8, U1.8
/P9: P2.9, U1.9
/P10: P2.10, U1.10
/P11: P2.11, U1.11
/P12: P2.12, U1.12
/P13: P1.3, P2.13, U1.13, U1.18
/P15: P2.15, U1.15
/P16: P1.1, U1.16
/P17: P1.2, U1.17
/P20: P1.5, U1.20
/P21: P1.6, U1.21
/P22: P1.7, U1.22
/P23: P1.8, U1.23
/P24: P1.9, U1.24
/P25: P1.10, U1.25
/P26: P1.11, U1.26
/P27: P1.12, U1.27
/RN_RESET: P1.15, U1.30, U2.32
/SS_UART_RX: P1.13, U1.28, U2.6
/SS_UART_TX: P1.14, U1.29, U2.7
Earth: P1.4, P2.14, U1.14, U1.19, U2.1, U2.8, U2.11, U2.20, U2.21, U2.22, U2.24, U2.26, U2.27, U2.28, U2.33, U2.41, U2.47
unnamed: P25.1, U2.25
unnamed: P26.1, U2.23
